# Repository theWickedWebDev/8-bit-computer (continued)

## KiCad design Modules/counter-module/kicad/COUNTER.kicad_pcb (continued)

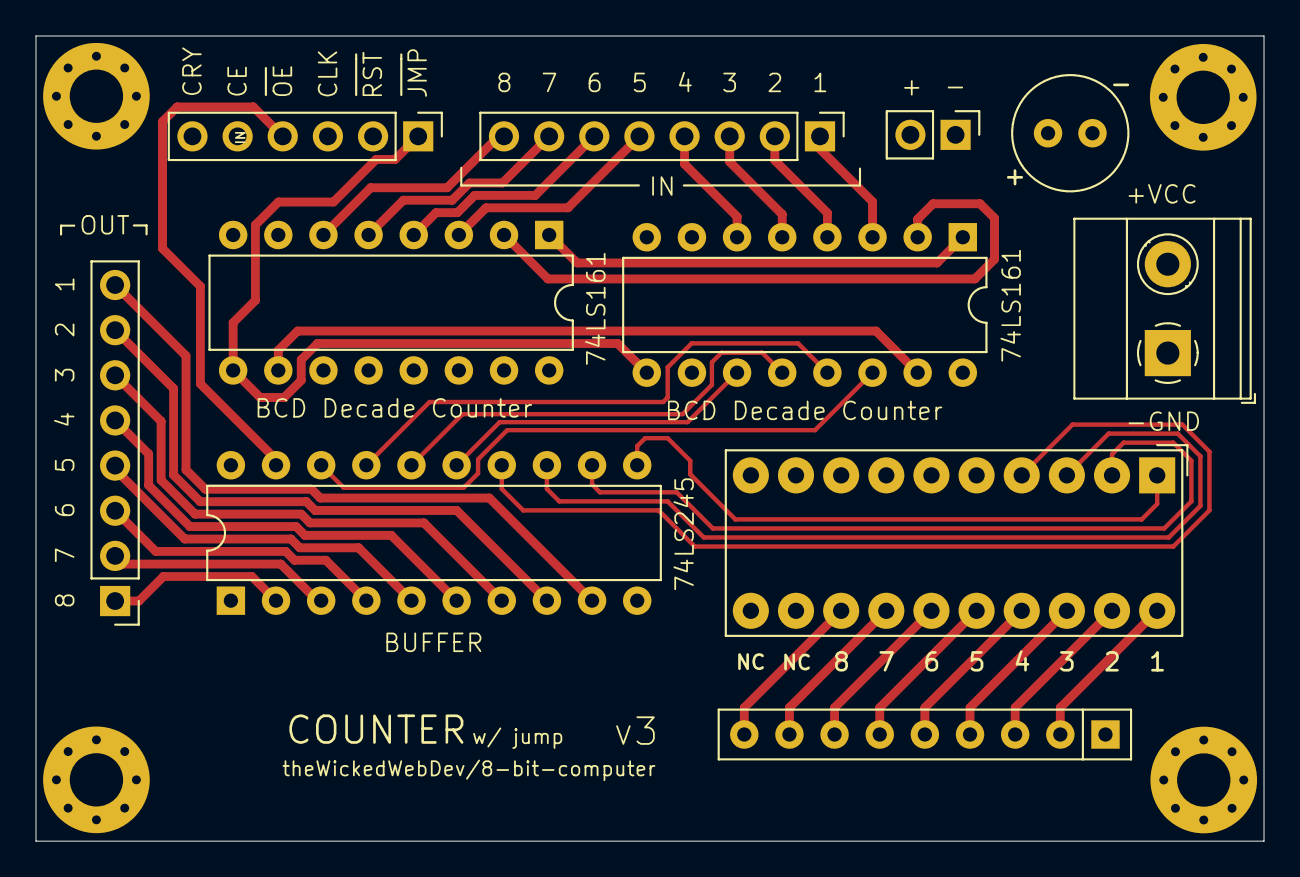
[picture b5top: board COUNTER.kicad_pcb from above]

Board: 4 copper layers, 69.1 x 45.3 mm, 11 parts (0 on the bottom side), 41 nets.

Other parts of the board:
C10: CP1; C_Radial_D6.3mm_H11.0mm_P2.50mm

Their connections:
GND: C10.2; also elsewhere on the board
VCC: C10.1; also elsewhere on the board

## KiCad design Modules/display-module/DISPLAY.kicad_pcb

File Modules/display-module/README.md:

# Display Module

MORE DETAILS TO COME

Uses a JK flip flop, a 555 timer and EEPROM to multiplex four 7-segment displays to output the current value of the bus in decimal.

<br/>

<br/><br/>

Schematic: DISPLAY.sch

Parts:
C16: CP1; CP_Radial_D6.3mm_P2.50mm
C133: CP; C_Disc_D6.0mm_W2.5mm_P5.00mm
C233: C; C_Disc_D6.0mm_W2.5mm_P5.00mm
J1: Screw_Terminal_01x02; TerminalBlock_Phoenix_MKDS-1,5-2_1x02_P5.00mm_Horizontal
J2: Conn_01x08; PinHeader_1x08_P2.54mm_Vertical
J3: Conn_01x05; PinHeader_1x05_P2.54mm_Vertical
R1, R1452, R2123: R_US; R_Axial_DIN0207_L6.3mm_D2.5mm_P10.16mm_Horizontal
SW1: SW_SPST; SW_DIP_SPSTx01_Slide_9.78x4.72mm_W7.62mm_P2.54mm
U1, U4, U5, U6: HDSP-7503; 7SegmentLED_LTS6760_LTS6780
U2: 74LS08; DIP-16_W7.62mm
U3: 74LS273; DIP-20_W7.62mm
U9: AT28C256; DIP_Socket-40_W11.9_W12.7_W15.24_W17.78_W18.5_3M_240-1280-0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
U1555: NE55P; DIP-8_W7.62mm
U2444: 74LS76; DIP-16_W7.62mm
U4332: 74LS139; DIP-16_W7.62mm

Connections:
1_DISPLAY: U6.3 (CC1), U6.8 (CC2), U4332.4 (O0)
10_DISPLAY: U5.3 (CC1), U5.8 (CC2), U4332.5 (O1)
100_DISPLAY: U4.3 (CC1), U4.8 (CC2), U4332.6 (O2)
A0: U9.25 (A8), U2444.6 (C), U2444.14 (~Q), U4332.2 (A0)
A1: U9.24 (A9), U2444.10 (~Q), U4332.3 (A1)
A_SEG: U1.7 (A), U4.7 (A), U5.7 (A), U6.7 (A), U9.18 (IO6)
BUS0: J2.8, U3.18 (D7)
BUS1: J2.7, U3.17 (D6)
BUS2: J2.6, U3.14 (D5)
BUS3: J2.5, U3.13 (D4)
BUS4: J2.4, U3.8 (D3)
BUS5: J2.3, U3.7 (D2)
BUS6: J2.2, U3.4 (D1)
BUS7: J2.1, U3.3 (D0)
B_SEG: U1.6 (B), U4.6 (B), U5.6 (B), U6.6 (B), U9.17 (IO5)
CLOCK: J3.3, U2.2
C_SEG: U1.4 (C), U4.4 (C), U5.4 (C), U6.4 (C), U9.16 (IO4)
DP_SEG: U1.5 (DP), U4.5 (DP), U5.5 (DP), U6.5 (DP), U9.19 (IO7)
D_SEG: U1.2 (D), U4.2 (D), U5.2 (D), U6.2 (D), U9.15 (IO3)
E_SEG: U1.1 (E), U4.1 (E), U5.1 (E), U6.1 (E), U9.13 (IO2)
F_SEG: U1.9 (F), U4.9 (F), U5.9 (F), U6.9 (F), U9.12 (IO1)
GND: C16.2, C133.1, C233.2, J1.2, R1.1, U2.7 (GND), U3.10 (GND), U9.1 (A14), U9.2 (A12), U9.14 (GND), U9.20 (~CE), U9.22 (~OE), U9.26 (A13), U1555.1 (GND), U2444.13 (GND), U4332.1 (E), U4332.8 (GND); also elsewhere on the board
G_SEG: U1.10 (G), U4.10 (G), U5.10 (G), U6.10 (G), U9.11 (IO0)
HEX: J3.1, U9.23 (A11); also elsewhere on the board
unnamed: C133.2, U1555.2 (TR)
unnamed: C233.1, U1555.5 (CV)
unnamed: R1452.1, R2123.1, U1555.7 (DIS)
unnamed: R1452.2, U1555.6 (THR)
unnamed: U2.3, U3.11 (Cp)
unnamed: U3.2 (Q0), U9.3 (A7)
unnamed: U3.5 (Q1), U9.4 (A6)
unnamed: U3.6 (Q2), U9.5 (A5)
unnamed: U3.9 (Q3), U9.6 (A4)
unnamed: U3.12 (Q4), U9.7 (A3)
unnamed: U3.15 (Q5), U9.8 (A2)
unnamed: U3.16 (Q6), U9.9 (A1)
unnamed: U3.19 (Q7), U9.10 (A0)
OI: J3.2, U2.1
RATE: U1555.3 (Q), U2444.1 (C)
RST: J3.4, U3.1 (~Mr)
SIGNED: J3.5, R1.2, SW1.2, U9.21 (A10)
SIGN_DISPLAY: U1.3 (CC1), U1.8 (CC2), U4332.7 (O3)
VCC: C16.1, J1.1, R2123.2, SW1.1, U2.14 (VCC), U3.20 (VCC), U9.27 (~WE), U9.28 (VCC), U1555.8 (VCC), U2444.2 (~S), U2444.3 (~R), U2444.4 (J), U2444.5 (VCC), U2444.7 (~S), U2444.8 (~R), U2444.9 (J), U2444.12 (K), U2444.16 (K), U4332.16 (VCC)

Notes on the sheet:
Power
Counter
Clock
Logic Gate Power
CONNECTIONS
SEGMENT DISPLAYS
REGISTER & EEPROM

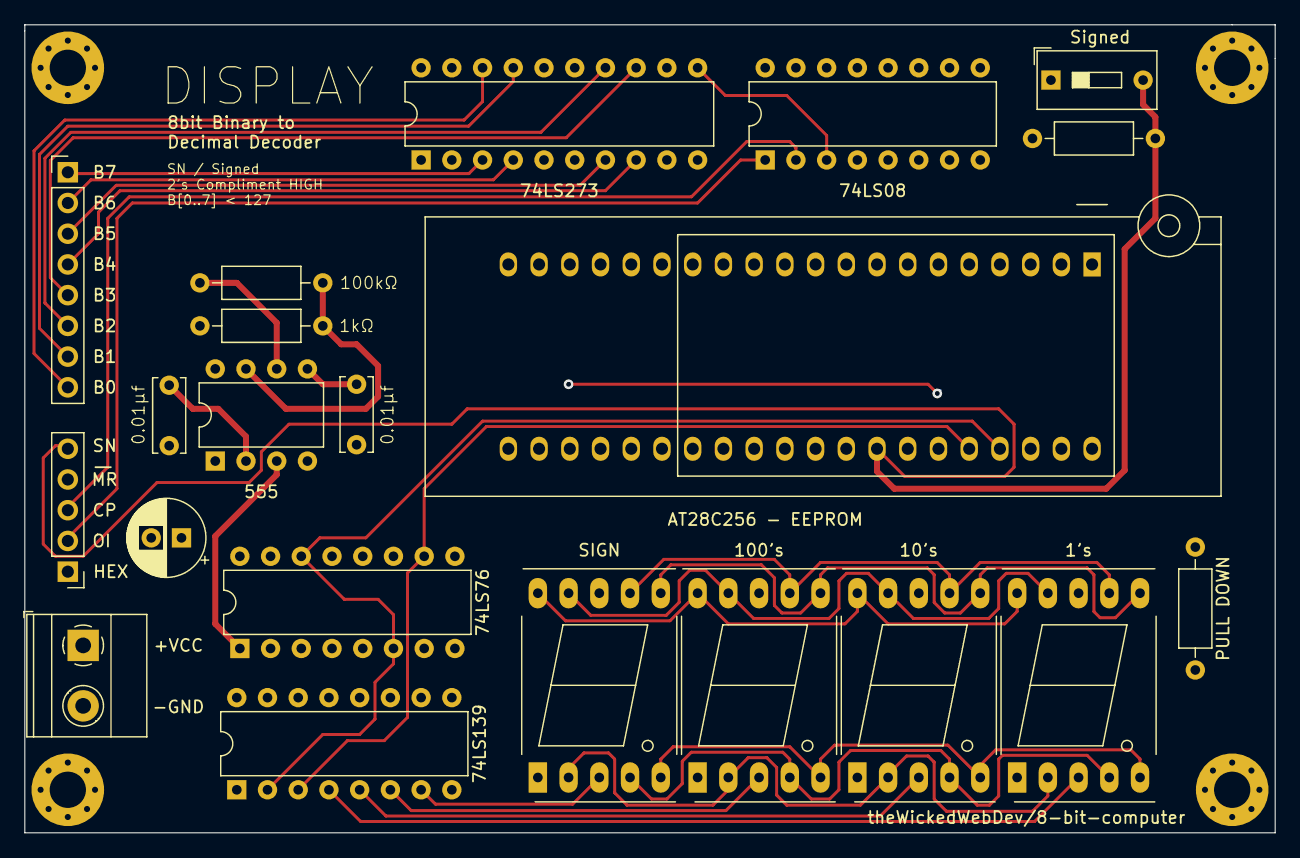
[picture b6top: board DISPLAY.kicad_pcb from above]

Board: 4 copper layers, 103.4 x 66.8 mm, 21 parts (0 on the bottom side), 43 nets.

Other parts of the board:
R2: R_US; R_Axial_DIN0207_L6.3mm_D2.5mm_P10.16mm_Horizontal

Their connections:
GND: R2.1; also elsewhere on the board
HEX: R2.2; also elsewhere on the board

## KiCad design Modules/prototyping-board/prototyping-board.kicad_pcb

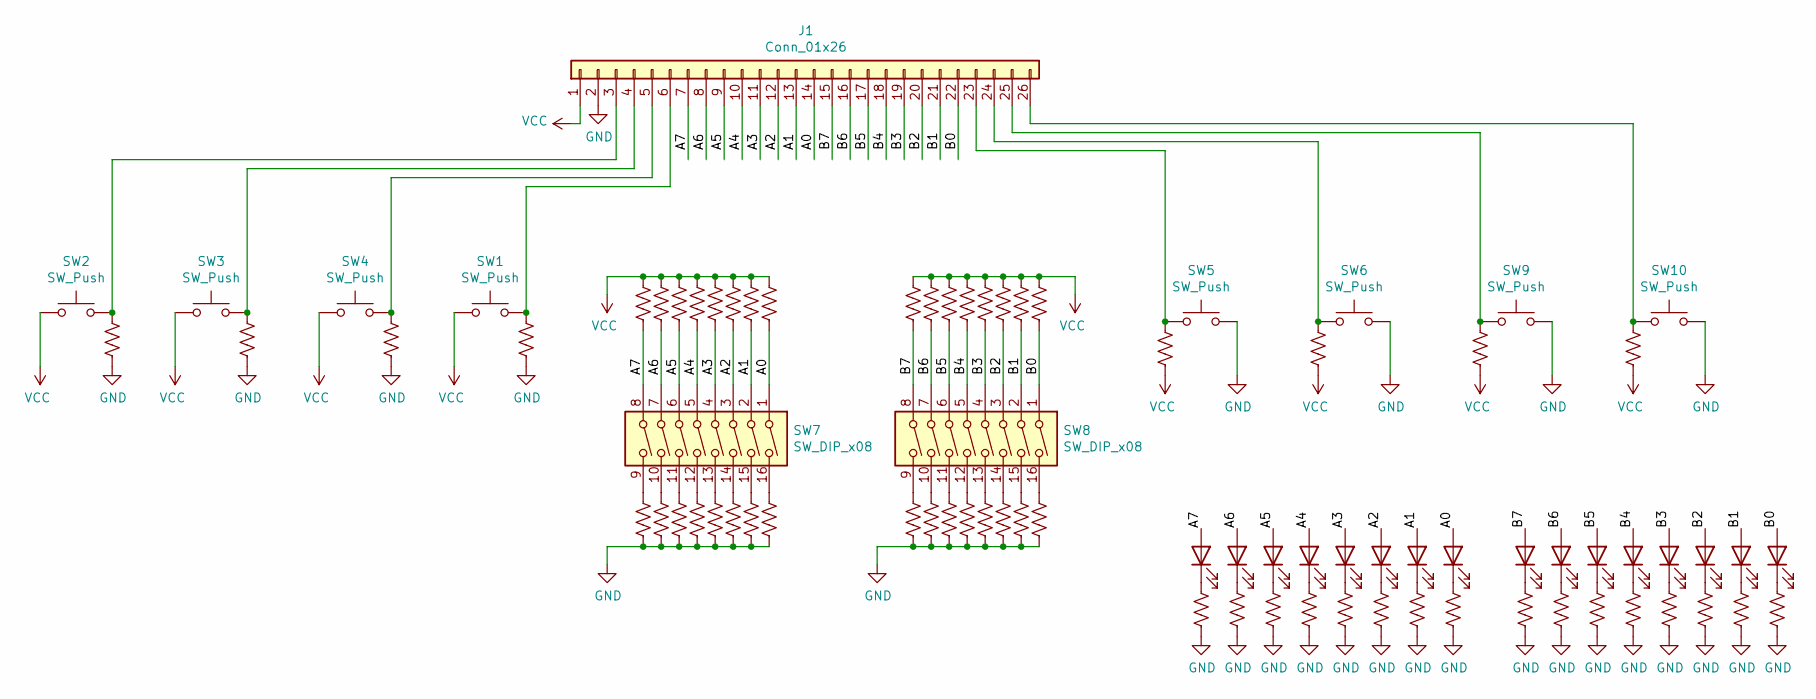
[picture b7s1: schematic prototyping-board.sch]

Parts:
D1, D2, D3, D4, D5, D6, D7, D8, D9, D10, D11, D12, D13, D14, D15, D16: LED; LED_0805_2012Metric
J1: Conn_01x26; PinHeader_1x26_P2.54mm_Horizontal
R1, R2, R3, R4, R5, R6, R7, R8, R9, R10, R11, R12, R13, R14, R15, R16, R17, R18, R19, R20, R21, R22, R23, R24, R25, R26, R27, R28, R29, R30, R31, R32, R33, R34, R35, R36, R37, R38, R39, R40, R41, R42, R43, R44, R45, R46, R47, R48, R49, R50, R51, R52, R53, R54, R55, R56: R_US; R_0805_2012Metric
SW1, SW2, SW3, SW4, SW5, SW6, SW9, SW10: SW_Push; SW_PUSH_6mm
SW7, SW8: SW_DIP_x08; SW_DIP_SPSTx08_Slide_9.78x22.5mm_W7.62mm_P2.54mm

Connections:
/A0: D8.2 (A), J1.14, R16.2, SW7.1
/A1: D7.2 (A), J1.13, R15.2, SW7.2
/A2: D6.2 (A), J1.12, R14.2, SW7.3
/A3: D5.2 (A), J1.11, R13.2, SW7.4
/A4: D4.2 (A), J1.10, R12.2, SW7.5
/A5: D3.2 (A), J1.9, R11.2, SW7.6
/A6: D2.2 (A), J1.8, R10.2, SW7.7
/A7: D1.2 (A), J1.7, R9.2, SW7.8
/B0: D16.2 (A), J1.22, R24.2, SW8.1
/B1: D15.2 (A), J1.21, R23.2, SW8.2
/B2: D14.2 (A), J1.20, R22.2, SW8.3
/B3: D13.2 (A), J1.19, R21.2, SW8.4
/B4: D12.2 (A), J1.18, R20.2, SW8.5
/B5: D11.2 (A), J1.17, R19.2, SW8.6
/B6: D10.2 (A), J1.16, R18.2, SW8.7
/B7: D9.2 (A), J1.15, R17.2, SW8.8
GND: J1.2, R1.2, R2.2, R3.2, R4.2, R5.2, R6.2, R7.2, R8.2, R25.2, R26.2, R27.2, R28.2, R29.2, R30.2, R31.2, R32.2, R33.2, R34.2, R35.2, R36.2, R41.2, R42.2, R43.2, R44.2, R45.2, R46.2, R47.2, R48.2, R49.2, R50.2, R51.2, R52.2, R53.2, R54.2, R55.2, R56.2, SW5.2, SW6.2, SW9.2, SW10.2
unnamed: D1.1 (K), R41.1
unnamed: D2.1 (K), R42.1
unnamed: D3.1 (K), R43.1
unnamed: D4.1 (K), R44.1
unnamed: D5.1 (K), R45.1
unnamed: D6.1 (K), R46.1
unnamed: D7.1 (K), R47.1
unnamed: D8.1 (K), R48.1
unnamed: D9.1 (K), R49.1
unnamed: D10.1 (K), R50.1
unnamed: D11.1 (K), R51.1
unnamed: D12.1 (K), R52.1
unnamed: D13.1 (K), R53.1
unnamed: D14.1 (K), R54.1
unnamed: D15.1 (K), R55.1
unnamed: D16.1 (K), R56.1
unnamed: J1.3, R33.1, SW2.2
unnamed: J1.4, R34.1, SW3.2
unnamed: J1.5, R35.1, SW4.2
unnamed: J1.6, R36.1, SW1.2
unnamed: J1.23, R37.1, SW5.1
unnamed: J1.24, R38.1, SW6.1
unnamed: J1.25, R39.1, SW9.1
unnamed: J1.26, R40.1, SW10.1
unnamed: R1.1, SW7.9
unnamed: R2.1, SW7.10
unnamed: R3.1, SW7.11
unnamed: R4.1, SW7.12
unnamed: R5.1, SW7.13
unnamed: R6.1, SW7.14
unnamed: R7.1, SW7.15
unnamed: R8.1, SW7.16
unnamed: R25.1, SW8.9
unnamed: R26.1, SW8.10
unnamed: R27.1, SW8.11
unnamed: R28.1, SW8.12
unnamed: R29.1, SW8.13
unnamed: R30.1, SW8.14
unnamed: R31.1, SW8.15
unnamed: R32.1, SW8.16
VCC: J1.1, R9.1, R10.1, R11.1, R12.1, R13.1, R14.1, R15.1, R16.1, R17.1, R18.1, R19.1, R20.1, R21.1, R22.1, R23.1, R24.1, R37.2, R38.2, R39.2, R40.2, SW1.1, SW2.1, SW3.1, SW4.1

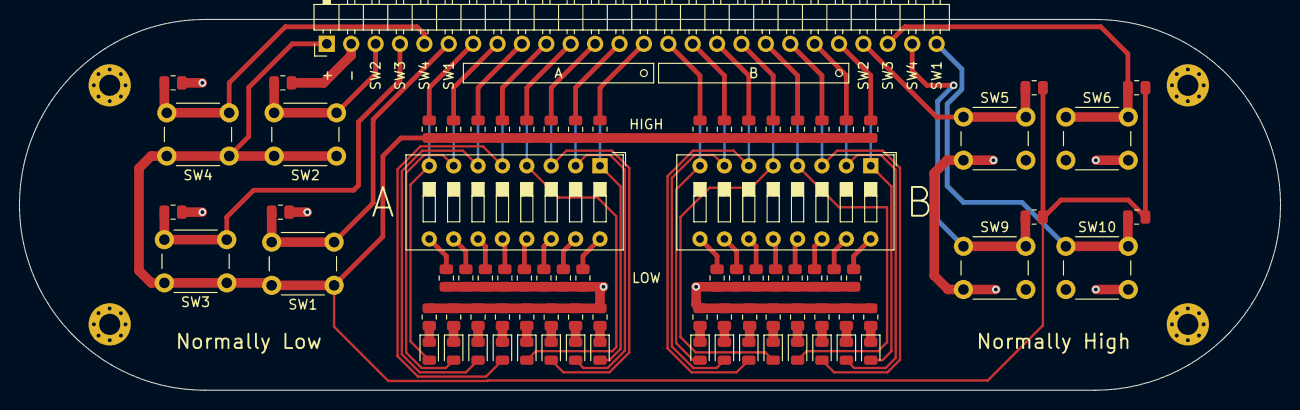
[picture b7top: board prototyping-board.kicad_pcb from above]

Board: 2 copper layers, 131.3 x 38.6 mm, 83 parts (0 on the bottom side), 58 nets.

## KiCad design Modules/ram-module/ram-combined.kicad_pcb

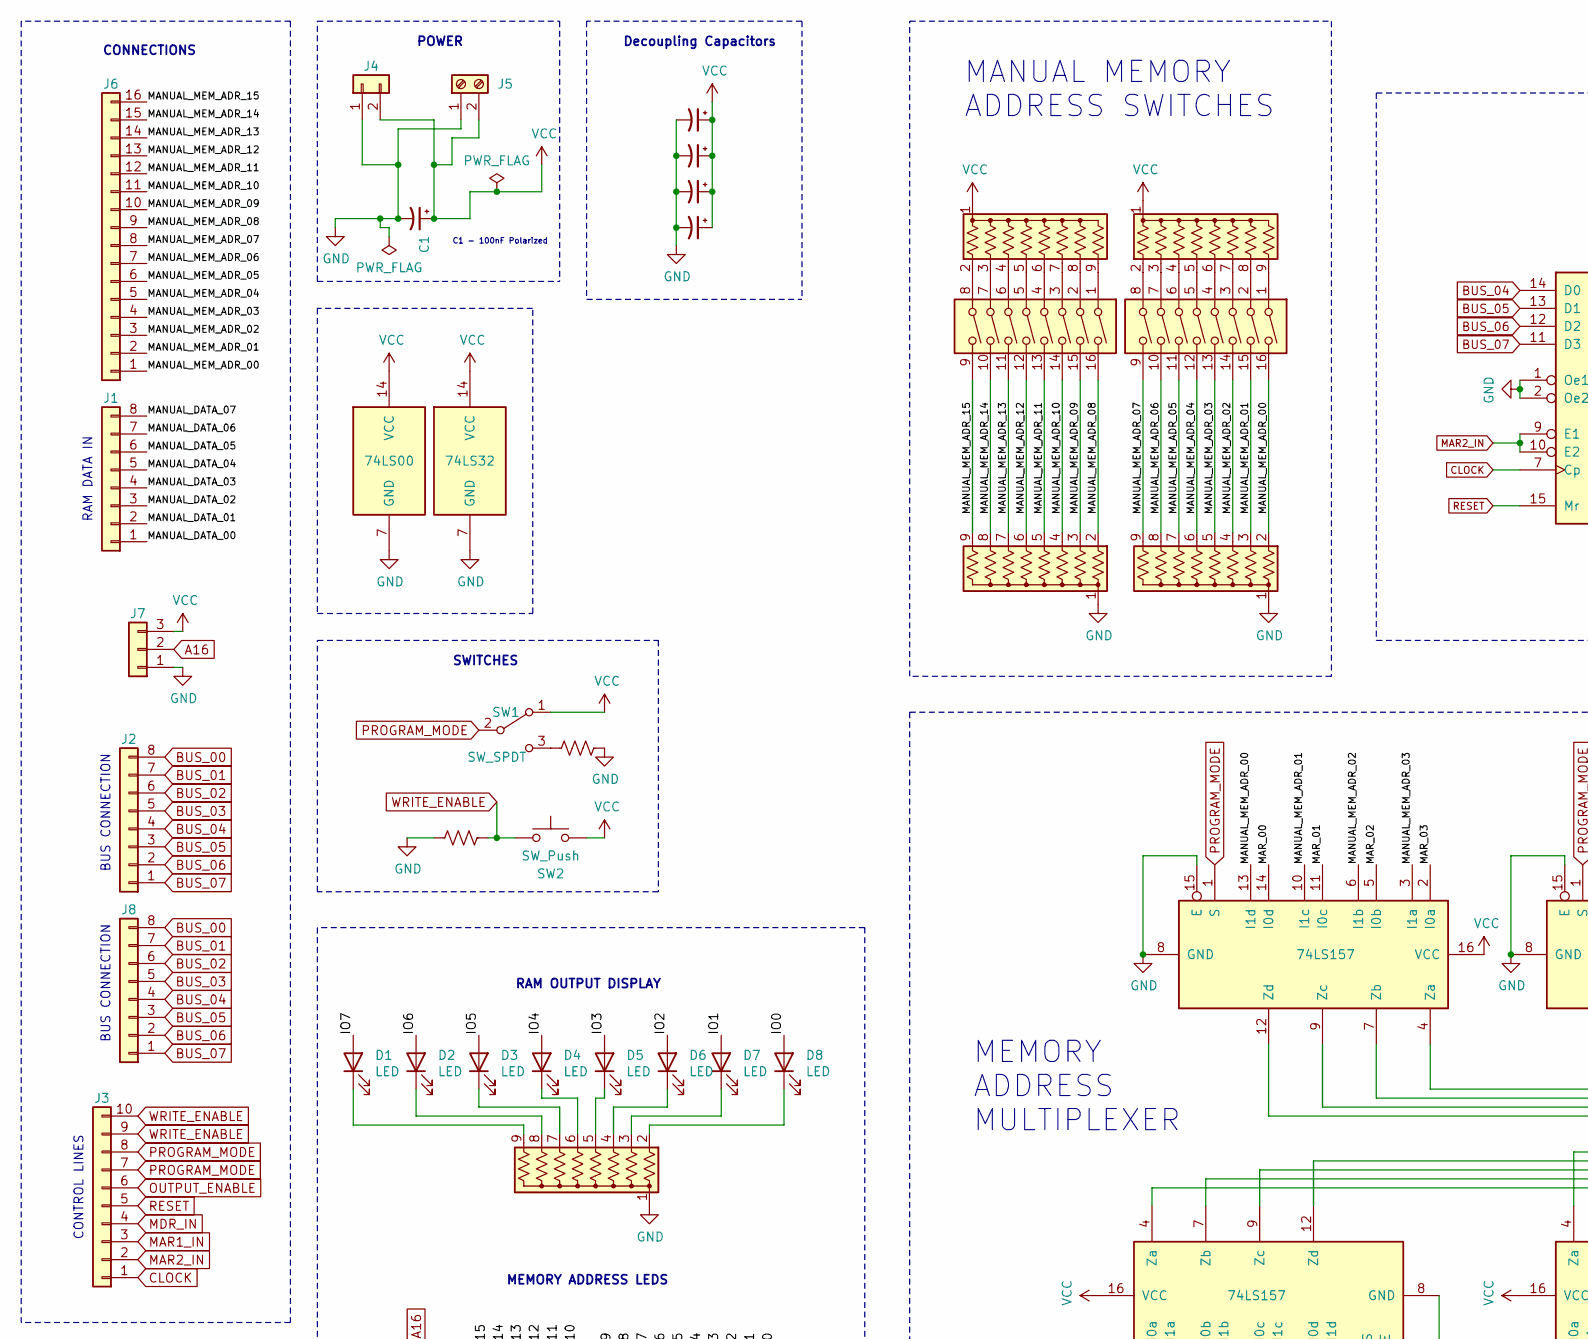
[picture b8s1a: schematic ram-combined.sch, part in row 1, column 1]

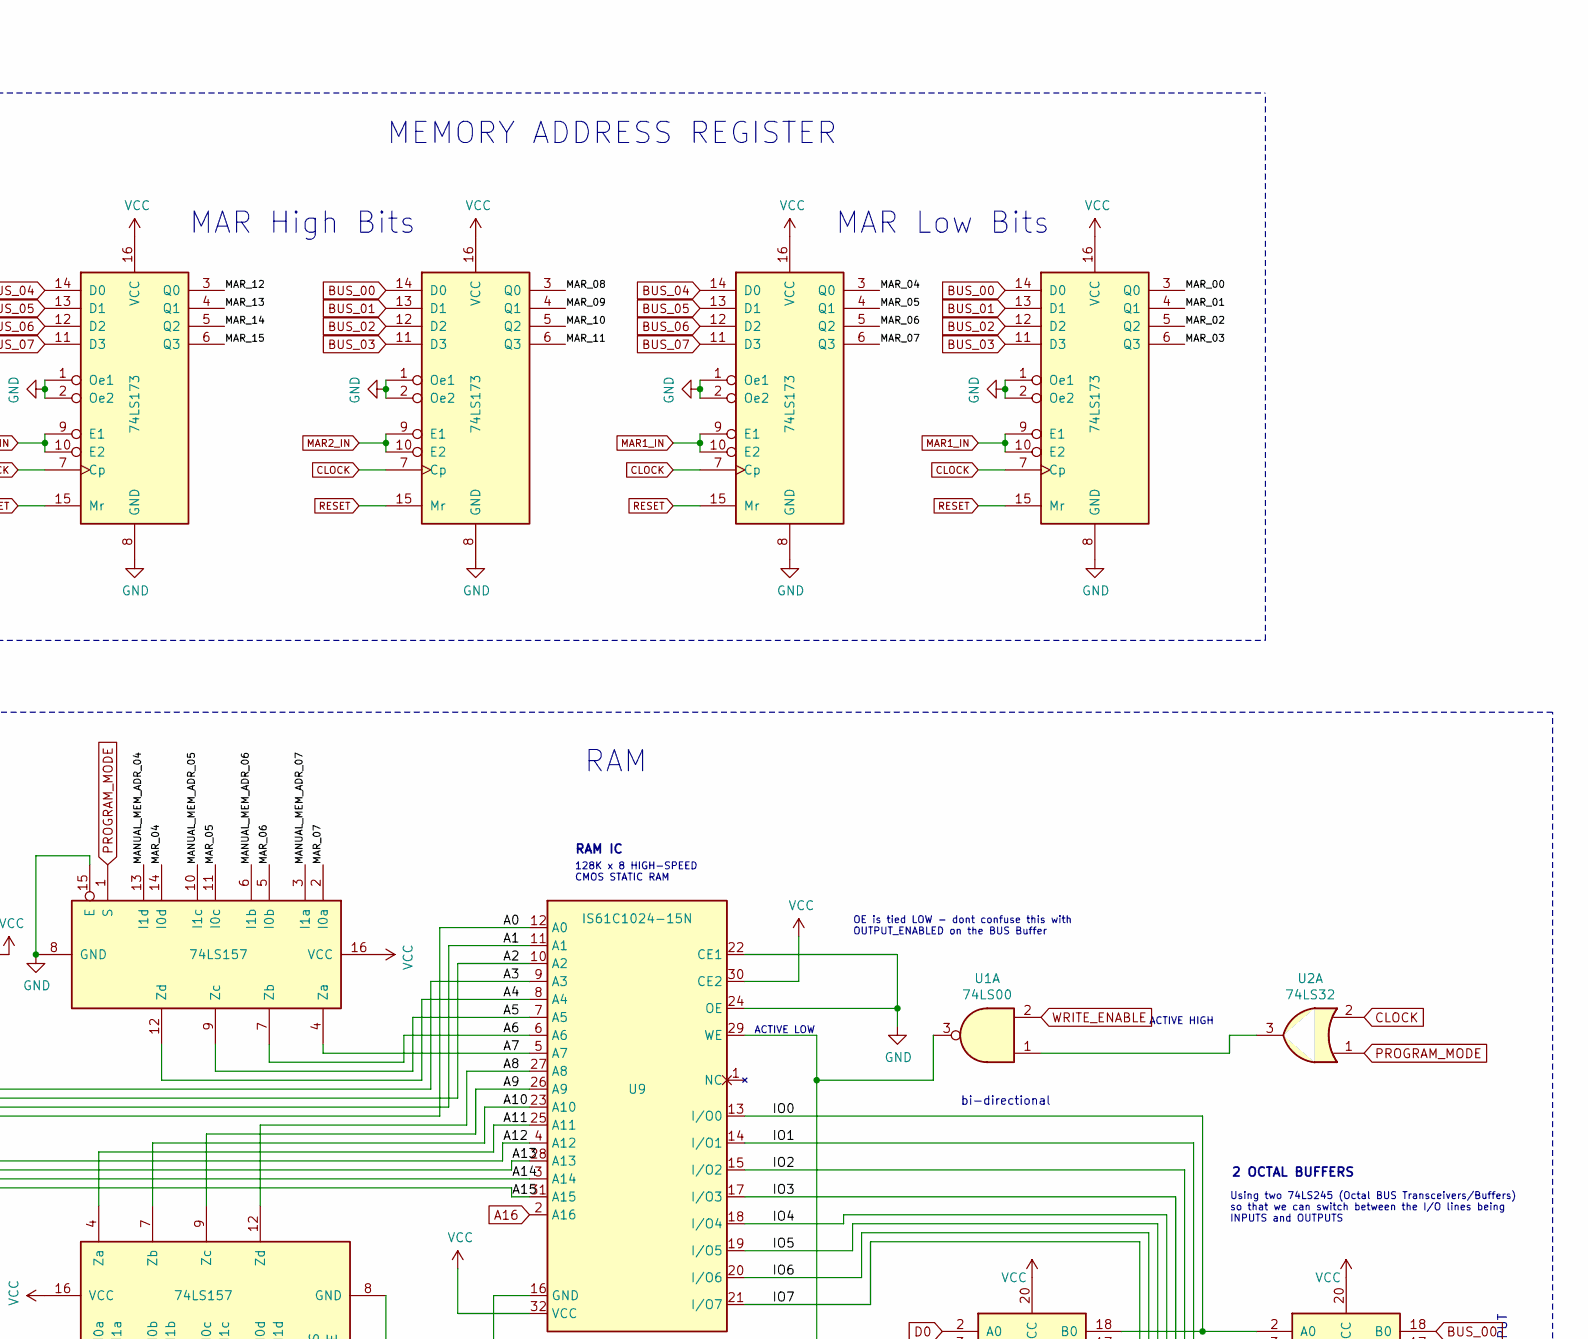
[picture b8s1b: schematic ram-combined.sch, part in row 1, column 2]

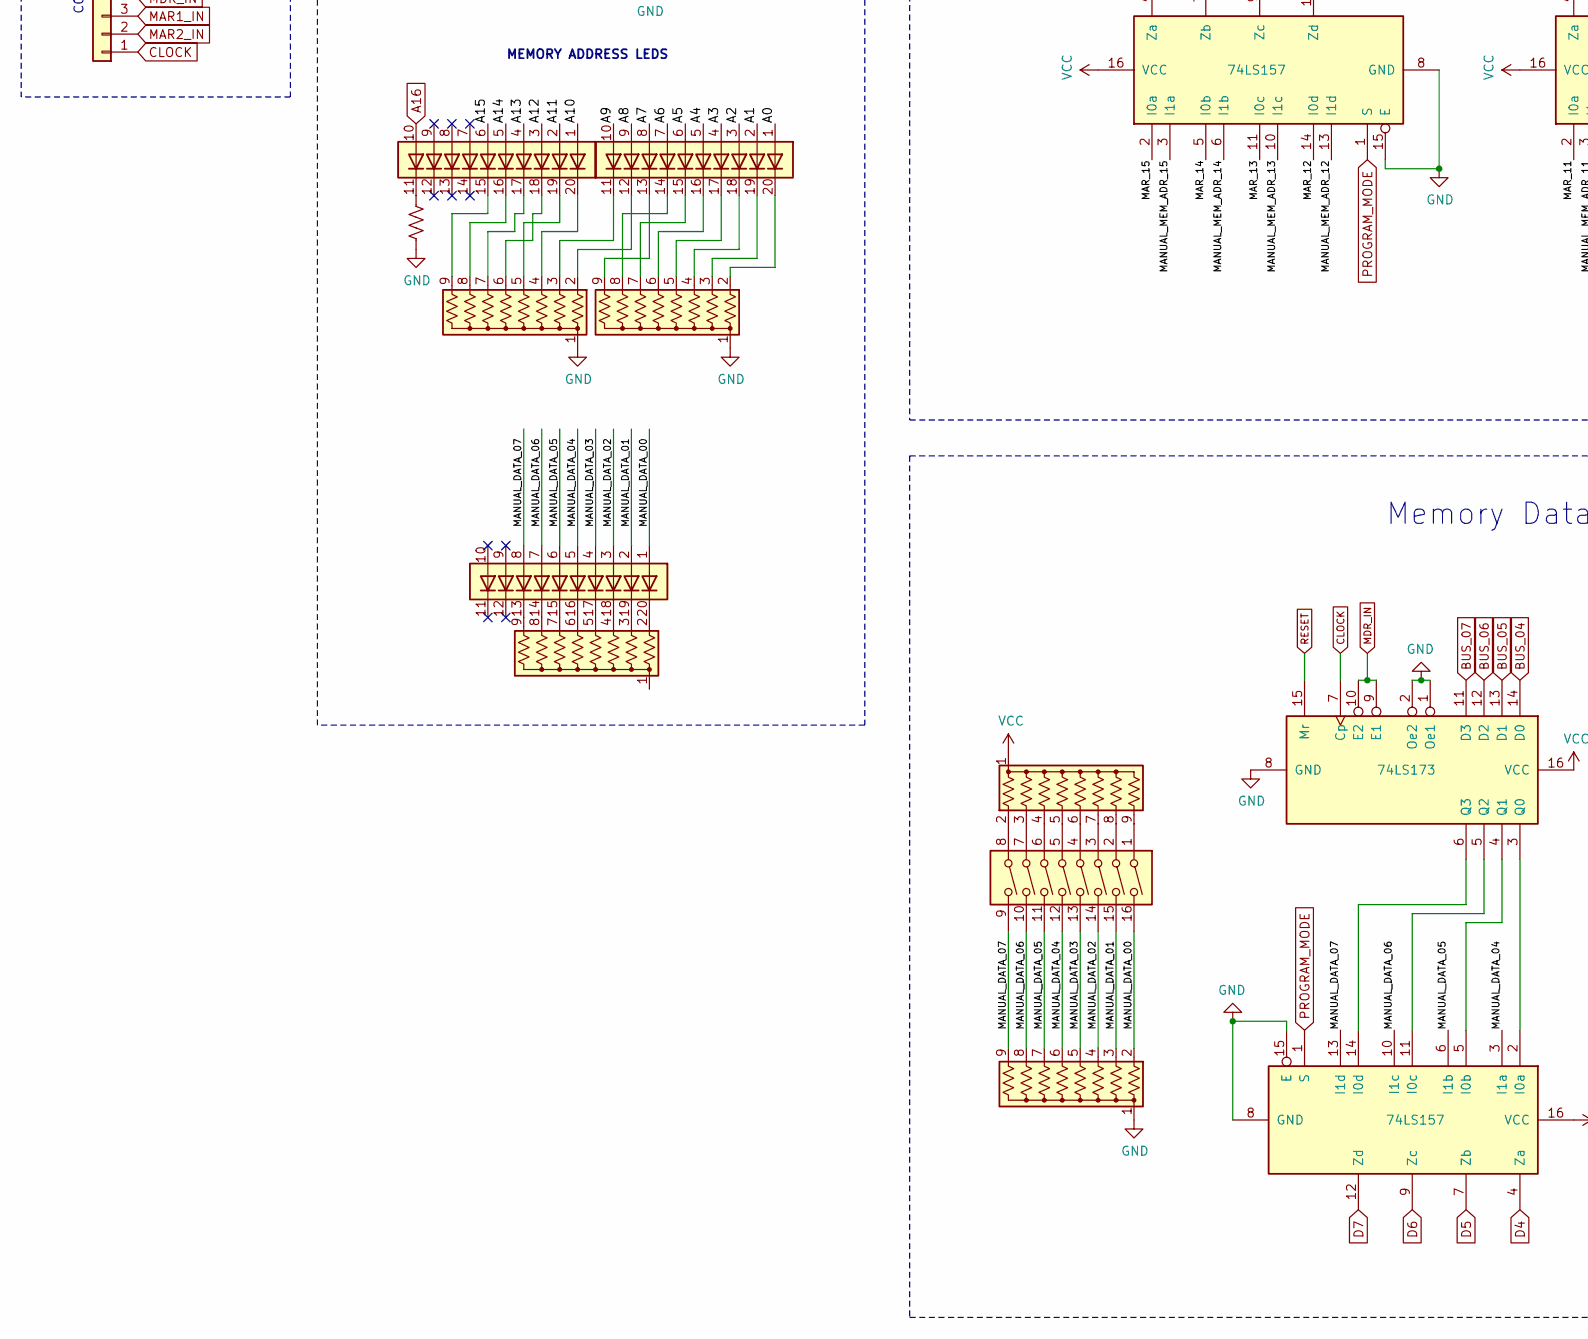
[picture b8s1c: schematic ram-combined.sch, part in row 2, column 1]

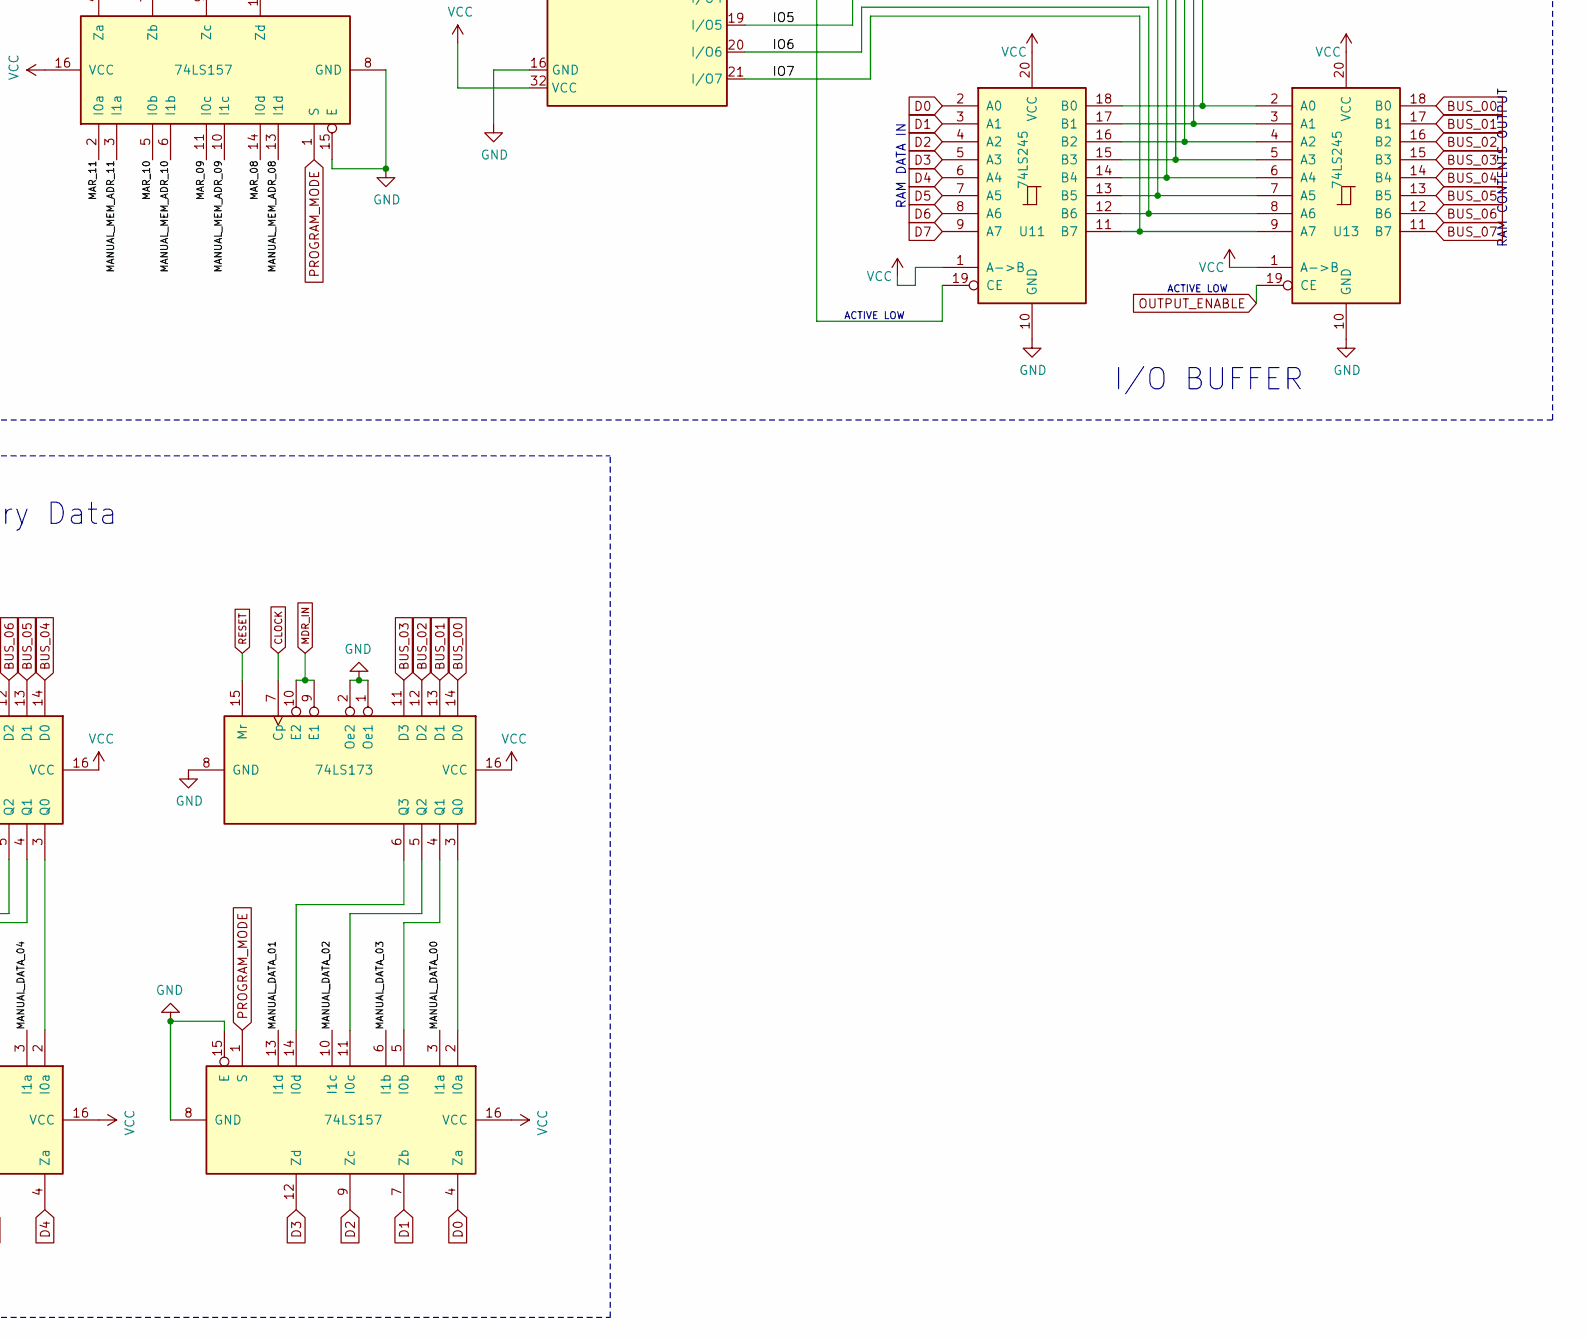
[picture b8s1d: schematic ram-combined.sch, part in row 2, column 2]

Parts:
BAR1, BAR2, BAR3: HDSP-4830_2; HDSP-4830
C1, C2, C3, C4, C5: CP1_Small; CP_Radial_D5.0mm_P2.50mm
D1, D2, D3, D4, D5, D6, D7, D8: LED; LED_D5.0mm
J1, J2, J8: Conn_01x08; PinHeader_1x08_P2.54mm_Vertical
J3: Conn_01x10; PinHeader_1x10_P2.54mm_Vertical
J4: Conn_01x02; PinHeader_1x02_P2.54mm_Vertical
J5: Screw_Terminal_01x02; TerminalBlock_Phoenix_MKDS-1,5-2_1x02_P5.00mm_Horizontal
J6: Conn_01x16; PinHeader_1x16_P2.54mm_Vertical
J7: Conn_01x08; PinHeader_1x03_P2.54mm_Vertical
R1, R2, R3: R_US; R_Axial_DIN0207_L6.3mm_D2.5mm_P10.16mm_Horizontal
RN1, RN2, RN3, RN4, RN5, RN6, RN7, RN8, RN9, RN10: R_Network08_US; R_Array_SIP9
SW1: SW_SPDT; PinHeader_1x03_P2.54mm_Vertical
SW2: SW_Push; SW_PUSH_6mm_H5mm
SW3, SW4, SW5: SW_DIP_x08; SW_DIP_SPSTx08_Slide_9.78x22.5mm_W7.62mm_P2.54mm
U1: 74LS00; DIP-14_W7.62mm
U2: 74LS32; DIP-14_W7.62mm
U3, U4, U6, U7, U15, U17: 74LS157; DIP-16_W7.62mm
U5, U8, U10, U12, U14, U16: 74LS173; DIP-16_W7.62mm
U9: IS61C1024-15N; DIP-32_W7.62mm
U11, U13: 74LS245; DIP-20_W7.62mm

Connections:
/A0: BAR2.1 (A), U4.12 (Zd), U9.12 (A0)
/A1: BAR2.2 (A), U4.9 (Zc), U9.11 (A1)
/A2: BAR2.3 (A), U4.7 (Zb), U9.10 (A2)
/A3: BAR2.4 (A), U4.4 (Za), U9.9 (A3)
/A4: BAR2.5 (A), U7.12 (Zd), U9.8 (A4)
/A5: BAR2.6 (A), U7.9 (Zc), U9.7 (A5)
/A6: BAR2.7 (A), U7.7 (Zb), U9.6 (A6)
/A7: BAR2.8 (A), U7.4 (Za), U9.5 (A7)
/A8: BAR2.9 (A), U6.12 (Zd), U9.27 (A8)
/A9: BAR2.10 (A), U6.9 (Zc), U9.26 (A9)
/A10: BAR1.1 (A), U6.7 (Zb), U9.23 (A10)
/A11: BAR1.2 (A), U6.4 (Za), U9.25 (A11)
/A12: BAR1.3 (A), U3.12 (Zd), U9.4 (A12)
/A13: BAR1.4 (A), U3.9 (Zc), U9.28 (A13)
/A14: BAR1.5 (A), U3.7 (Zb), U9.3 (A14)
/A15: BAR1.6 (A), U3.4 (Za), U9.31 (A15)
/IO0: D8.2 (A), U9.13 (I/O0), U11.18 (B0), U13.2 (A0)
/IO1: D7.2 (A), U9.14 (I/O1), U11.17 (B1), U13.3 (A1)
/IO2: D6.2 (A), U9.15 (I/O2), U11.16 (B2), U13.4 (A2)
/IO3: D5.2 (A), U9.17 (I/O3), U11.15 (B3), U13.5 (A3)
/IO4: D4.2 (A), U9.18 (I/O4), U11.14 (B4), U13.6 (A4)
/IO5: D3.2 (A), U9.19 (I/O5), U11.13 (B5), U13.7 (A5)
/IO6: D2.2 (A), U9.20 (I/O6), U11.12 (B6), U13.8 (A6)
/IO7: D1.2 (A), U9.21 (I/O7), U11.11 (B7), U13.9 (A7)
/MANUAL_DATA_00: BAR3.1 (A), J1.1, RN8.2 (R1), SW5.16, U17.3 (I1a)
/MANUAL_DATA_01: BAR3.2 (A), J1.2, RN8.3 (R2), SW5.15, U17.13 (I1d)
/MANUAL_DATA_02: BAR3.3 (A), J1.3, RN8.4 (R3), SW5.14, U17.10 (I1c)
/MANUAL_DATA_03: BAR3.4 (A), J1.4, RN8.5 (R4), SW5.13, U17.6 (I1b)
/MANUAL_DATA_04: BAR3.5 (A), J1.5, RN8.6 (R5), SW5.12, U15.3 (I1a)
/MANUAL_DATA_05: BAR3.6 (A), J1.6, RN8.7 (R6), SW5.11, U15.6 (I1b)
/MANUAL_DATA_06: BAR3.7 (A), J1.7, RN8.8 (R7), SW5.10, U15.10 (I1c)
/MANUAL_DATA_07: BAR3.8 (A), J1.8, RN8.9 (R8), SW5.9, U15.13 (I1d)
/MANUAL_MEM_ADR_00: J6.1, RN6.2 (R1), SW4.16, U4.13 (I1d)
/MANUAL_MEM_ADR_01: J6.2, RN6.3 (R2), SW4.15, U4.10 (I1c)
/MANUAL_MEM_ADR_02: J6.3, RN6.4 (R3), SW4.14, U4.6 (I1b)
/MANUAL_MEM_ADR_03: J6.4, RN6.5 (R4), SW4.13, U4.3 (I1a)
/MANUAL_MEM_ADR_04: J6.5, RN6.6 (R5), SW4.12, U7.13 (I1d)
/MANUAL_MEM_ADR_05: J6.6, RN6.7 (R6), SW4.11, U7.10 (I1c)
/MANUAL_MEM_ADR_06: J6.7, RN6.8 (R7), SW4.10, U7.6 (I1b)
/MANUAL_MEM_ADR_07: J6.8, RN6.9 (R8), SW4.9, U7.3 (I1a)
/MANUAL_MEM_ADR_08: J6.9, RN4.2 (R1), SW3.16, U6.13 (I1d)
/MANUAL_MEM_ADR_09: J6.10, RN4.3 (R2), SW3.15, U6.10 (I1c)
/MANUAL_MEM_ADR_10: J6.11, RN4.4 (R3), SW3.14, U6.6 (I1b)
/MANUAL_MEM_ADR_11: J6.12, RN4.5 (R4), SW3.13, U6.3 (I1a)
/MANUAL_MEM_ADR_12: J6.13, RN4.6 (R5), SW3.12, U3.13 (I1d)
/MANUAL_MEM_ADR_13: J6.14, RN4.7 (R6), SW3.11, U3.10 (I1c)
/MANUAL_MEM_ADR_14: J6.15, RN4.8 (R7), SW3.10, U3.6 (I1b)
/MANUAL_MEM_ADR_15: J6.16, RN4.9 (R8), SW3.9, U3.3 (I1a)
/MAR_00: U4.14 (I0d), U12.3 (Q0)
/MAR_01: U4.11 (I0c), U12.4 (Q1)
/MAR_02: U4.5 (I0b), U12.5 (Q2)
/MAR_03: U4.2 (I0a), U12.6 (Q3)
/MAR_04: U7.14 (I0d), U10.3 (Q0)
/MAR_05: U7.11 (I0c), U10.4 (Q1)
/MAR_06: U7.5 (I0b), U10.5 (Q2)
/MAR_07: U7.2 (I0a), U10.6 (Q3)
/MAR_08: U6.14 (I0d), U8.3 (Q0)
/MAR_09: U6.11 (I0c), U8.4 (Q1)
/MAR_10: U6.5 (I0b), U8.5 (Q2)
/MAR_11: U6.2 (I0a), U8.6 (Q3)
/MAR_12: U3.14 (I0d), U5.3 (Q0)
/MAR_13: U3.11 (I0c), U5.4 (Q1)
/MAR_14: U3.5 (I0b), U5.5 (Q2)
/MAR_15: U3.2 (I0a), U5.6 (Q3)
A16: BAR1.10 (A), J7.2, U9.2 (A16)
BUS_00: J2.8, J8.8, U8.14 (D0), U12.14 (D0), U13.18 (B0), U16.14 (D0)
BUS_01: J2.7, J8.7, U8.13 (D1), U12.13 (D1), U13.17 (B1), U16.13 (D1)
BUS_02: J2.6, J8.6, U8.12 (D2), U12.12 (D2), U13.16 (B2), U16.12 (D2)
BUS_03: J2.5, J8.5, U8.11 (D3), U12.11 (D3), U13.15 (B3), U16.11 (D3)
BUS_04: J2.4, J8.4, U5.14 (D0), U10.14 (D0), U13.14 (B4), U14.14 (D0)
BUS_05: J2.3, J8.3, U5.13 (D1), U10.13 (D1), U13.13 (B5), U14.13 (D1)
BUS_06: J2.2, J8.2, U5.12 (D2), U10.12 (D2), U13.12 (B6), U14.12 (D2)
BUS_07: J2.1, J8.1, U5.11 (D3), U10.11 (D3), U13.11 (B7), U14.11 (D3)
CLOCK: J3.1, U2.2, U5.7 (Cp), U8.7 (Cp), U10.7 (Cp), U12.7 (Cp), U14.7 (Cp), U16.7 (Cp)
D0: U11.2 (A0), U17.4 (Za)
D1: U11.3 (A1), U17.7 (Zb)
D2: U11.4 (A2), U17.9 (Zc)
D3: U11.5 (A3), U17.12 (Zd)
D4: U11.6 (A4), U15.4 (Za)
D5: U11.7 (A5), U15.7 (Zb)
D6: U11.8 (A6), U15.9 (Zc)
D7: U11.9 (A7), U15.12 (Zd)
GND: C1.2, C2.2, C3.2, C4.2, C5.2, J4.1, J5.1, J7.1, R1.2, R2.2, R3.1, RN1.1 (common), RN2.1 (common), RN3.1 (common), RN4.1 (common), RN6.1 (common), RN8.1 (common), U1.7 (GND), U2.7 (GND), U3.8 (GND), U3.15 (E), U4.8 (GND), U4.15 (E), U5.1 (Oe1), U5.2 (Oe2), U5.8 (GND), U6.8 (GND), U6.15 (E), U7.8 (GND), U7.15 (E), U8.1 (Oe1), U8.2 (Oe2), U8.8 (GND), U9.16 (GND), U9.22 (CE1), U9.24 (OE), U10.1 (Oe1), U10.2 (Oe2), U10.8 (GND), U11.10 (GND), U12.1 (Oe1), U12.2 (Oe2), U12.8 (GND), U13.10 (GND), U14.1 (Oe1), U14.2 (Oe2), U14.8 (GND), U15.8 (GND), U15.15 (E), U16.1 (Oe1), U16.2 (Oe2), U16.8 (GND), U17.8 (GND), U17.15 (E)
MAR1_IN: J3.3, U10.9 (E1), U10.10 (E2), U12.9 (E1), U12.10 (E2)
MAR2_IN: J3.2, U5.9 (E1), U5.10 (E2), U8.9 (E1), U8.10 (E2)
MDR_IN: J3.4, U14.9 (E1), U14.10 (E2), U16.9 (E1), U16.10 (E2)
unnamed: BAR1.11 (K), R1.1
unnamed: BAR1.15 (K), RN1.9 (R8)
unnamed: BAR1.16 (K), RN1.8 (R7)
unnamed: BAR1.17 (K), RN1.7 (R6)
unnamed: BAR1.18 (K), RN1.6 (R5)
unnamed: BAR1.19 (K), RN1.5 (R4)
unnamed: BAR1.20 (K), RN1.4 (R3)
unnamed: BAR2.11 (K), RN1.3 (R2)
unnamed: BAR2.12 (K), RN1.2 (R1)
unnamed: BAR2.13 (K), RN3.9 (R8)
unnamed: BAR2.14 (K), RN3.8 (R7)
unnamed: BAR2.15 (K), RN3.7 (R6)
unnamed: BAR2.16 (K), RN3.6 (R5)
unnamed: BAR2.17 (K), RN3.5 (R4)
unnamed: BAR2.18 (K), RN3.4 (R3)
unnamed: BAR2.19 (K), RN3.3 (R2)
unnamed: BAR2.20 (K), RN3.2 (R1)
unnamed: BAR3.13 (K), RN10.9 (R8)
unnamed: BAR3.14 (K), RN10.8 (R7)
unnamed: BAR3.15 (K), RN10.7 (R6)
unnamed: BAR3.16 (K), RN10.6 (R5)
unnamed: BAR3.17 (K), RN10.5 (R4)
unnamed: BAR3.18 (K), RN10.4 (R3)
unnamed: BAR3.19 (K), RN10.3 (R2)
unnamed: BAR3.20 (K), RN10.2 (R1)
unnamed: D1.1 (K), RN2.9 (R8)
unnamed: D2.1 (K), RN2.8 (R7)
unnamed: D3.1 (K), RN2.7 (R6)
unnamed: D4.1 (K), RN2.6 (R5)
unnamed: D5.1 (K), RN2.5 (R4)
unnamed: D6.1 (K), RN2.4 (R3)
unnamed: D7.1 (K), RN2.3 (R2)
unnamed: D8.1 (K), RN2.2 (R1)
unnamed: R3.2, SW1.3 (C)
unnamed: RN5.2 (R1), SW3.8
unnamed: RN5.3 (R2), SW3.7
unnamed: RN5.4 (R3), SW3.6
unnamed: RN5.5 (R4), SW3.5
unnamed: RN5.6 (R5), SW3.4
unnamed: RN5.7 (R6), SW3.3
unnamed: RN5.8 (R7), SW3.2
unnamed: RN5.9 (R8), SW3.1
unnamed: RN7.2 (R1), SW4.8
unnamed: RN7.3 (R2), SW4.7
unnamed: RN7.4 (R3), SW4.6
unnamed: RN7.5 (R4), SW4.5
unnamed: RN7.6 (R5), SW4.4
unnamed: RN7.7 (R6), SW4.3
unnamed: RN7.8 (R7), SW4.2
unnamed: RN7.9 (R8), SW4.1
unnamed: RN9.2 (R1), SW5.8
unnamed: RN9.3 (R2), SW5.7
unnamed: RN9.4 (R3), SW5.6
unnamed: RN9.5 (R4), SW5.5
unnamed: RN9.6 (R5), SW5.4
unnamed: RN9.7 (R6), SW5.3
unnamed: RN9.8 (R7), SW5.2
unnamed: RN9.9 (R8), SW5.1
unnamed: U1.1, U2.3
unnamed: U1.3, U9.29 (WE), U11.19 (CE)
unnamed: U14.3 (Q0), U15.2 (I0a)
unnamed: U14.4 (Q1), U15.5 (I0b)
unnamed: U14.5 (Q2), U15.11 (I0c)
unnamed: U14.6 (Q3), U15.14 (I0d)
unnamed: U16.3 (Q0), U17.2 (I0a)
unnamed: U16.4 (Q1), U17.5 (I0b)
unnamed: U16.5 (Q2), U17.11 (I0c)
unnamed: U16.6 (Q3), U17.14 (I0d)
OUTPUT_ENABLE: J3.6, U13.19 (CE)
PROGRAM_MODE: J3.7, J3.8, SW1.2 (B), U2.1, U3.1 (S), U4.1 (S), U6.1 (S), U7.1 (S), U15.1 (S), U17.1 (S)
RESET: J3.5, U5.15 (Mr), U8.15 (Mr), U10.15 (Mr), U12.15 (Mr), U14.15 (Mr), U16.15 (Mr)
VCC: C1.1, C2.1, C3.1, C4.1, C5.1, J4.2, J5.2, J7.3, RN5.1 (common), RN7.1 (common), RN9.1 (common), SW1.1 (A), SW2.2, U1.14 (VCC), U2.14 (VCC), U3.16 (VCC), U4.16 (VCC), U5.16 (VCC), U6.16 (VCC), U7.16 (VCC), U8.16 (VCC), U9.30 (CE2), U9.32 (VCC), U10.16 (VCC), U11.1 (A->B), U11.20 (VCC), U12.16 (VCC), U13.1 (A->B), U13.20 (VCC), U14.16 (VCC), U15.16 (VCC), U16.16 (VCC), U17.16 (VCC)
WRITE_ENABLE: J3.9, J3.10, R2.1, SW2.1, U1.2

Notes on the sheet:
MAR Low Bits
MAR High Bits
MEMORY ADDRESS MULTIPLEXER
MANUAL MEMORY ADDRESS SWITCHES
RAM CONTENTS OUTPUT
RAM DATA IN
RAM IC
2 OCTAL BUFFERS
ACTIVE LOW
POWER
RAM OUTPUT DISPLAY
Decoupling Capacitors
C1 - 100nF Polarized
CONTROL LINES
CONNECTIONS
BUS CONNECTION
bi-directional
Using two 74LS245 (Octal BUS Transceivers/Buffers) so that we can switch between the I/O lines being INPUTS and OUTPUTS
OE is tied LOW - dont confuse this with OUTPUT_ENABLED on the BUS Buffer
128K x 8 HIGH-SPEED CMOS STATIC RAM
ACTIVE HIGH
MEMORY ADDRESS LEDS
MEMORY ADDRESS REGISTER
RAM
I/O BUFFER
Memory Data
SWITCHES

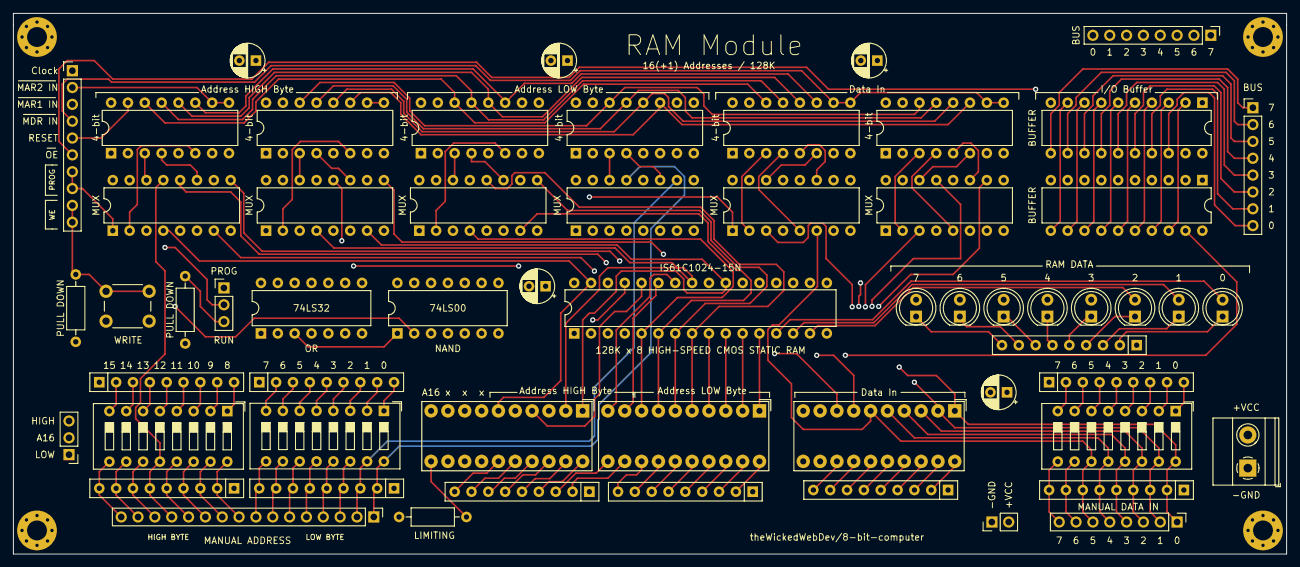
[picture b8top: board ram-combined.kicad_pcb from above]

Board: 4 copper layers, 192.0 x 81.5 mm, 59 parts (0 on the bottom side), 159 nets.
